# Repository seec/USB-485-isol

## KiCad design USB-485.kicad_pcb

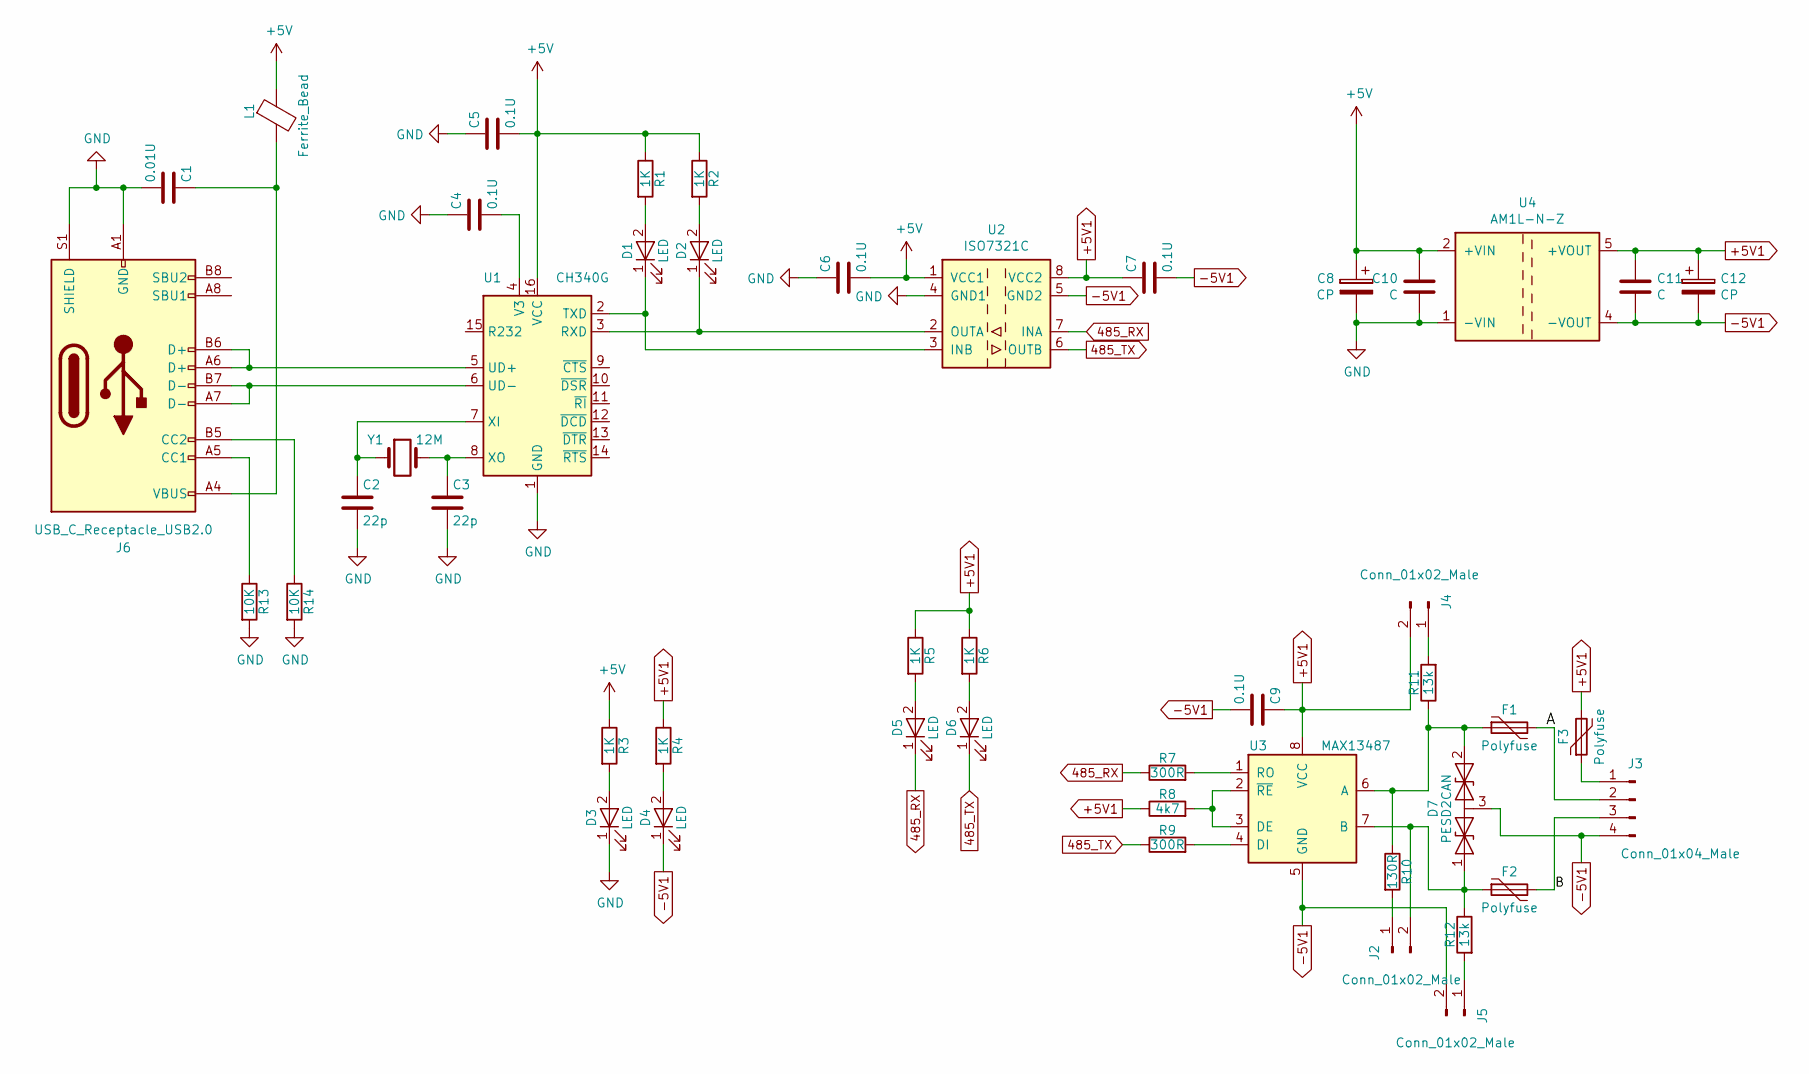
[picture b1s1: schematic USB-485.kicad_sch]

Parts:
C1: 0.01U; C_0805_2012Metric_Pad1.18x1.45mm_HandSolder
C2, C3: 22p; C_0805_2012Metric_Pad1.18x1.45mm_HandSolder
C4, C5, C6, C7, C9: 0.1U; C_0805_2012Metric_Pad1.18x1.45mm_HandSolder
C8, C12: CP; CP_Elec_5x5.3
C10, C11: C; C_0805_2012Metric_Pad1.18x1.45mm_HandSolder
D1, D2, D3, D4, D5, D6: LED; LED_D3.0mm
D7: PESD2CAN; SOT-23
F1, F2, F3: Polyfuse; Fuseholder_Littelfuse_Nano2_157x
J2, J4, J5: Conn_01x02_Male; PinHeader_1x02_P2.54mm_Vertical
J3: Conn_01x04_Male; TerminalBlock_MetzConnect_Type011_RT05504HBWC_1x04_P5.00mm_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
J6: USB_C_Receptacle_USB2.0; USB_C_Receptacle_HRO_TYPE-C-31-M-12
L1: Ferrite_Bead; L_Bourns-SRN4018
R1, R2, R3, R4, R5, R6: 1K; R_0805_2012Metric_Pad1.20x1.40mm_HandSolder
R7, R9: 300R; R_0805_2012Metric_Pad1.20x1.40mm_HandSolder
R8: 4k7; R_0805_2012Metric_Pad1.20x1.40mm_HandSolder
R10: 130R; R_0805_2012Metric_Pad1.20x1.40mm_HandSolder
R11, R12: 13k; R_0805_2012Metric_Pad1.20x1.40mm_HandSolder
R13, R14: 10K; R_0805_2012Metric_Pad1.20x1.40mm_HandSolder
U1: CH340G; SOIC-16_3.9x9.9mm_P1.27mm
U2: ISO7321C; SOIC-8_3.9x4.9mm_P1.27mm
U3: MAX13487; SOIC-8_3.9x4.9mm_P1.27mm
U4: AM1L-N-Z
Y1: 12M; Crystal_SMD_5032-2Pin_5.0x3.2mm

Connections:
485_RX: D5.1 (K), R7.1, U2.7 (INA)
485_TX: D6.1 (K), R9.1, U2.6 (OUTB)
+5V: C5.2, C6.2, C8.1, C10.1, L1.1, R1.1, R2.1, R3.1, U1.16 (VCC), U2.1 (VCC1), U4.2 (+VIN)
+5V1: C7.1, C9.1, C11.1, C12.1, F3.2, J4.2, R4.1, R5.1, R6.1, R8.1, U2.8 (VCC2), U3.8 (VCC), U4.5 (+VOUT)
-5V1: C7.2, C9.2, C11.2, C12.2, D4.1 (K), D7.3 (common), J3.4, J5.2, U2.5 (GND2), U3.5 (GND), U4.4 (-VOUT)
/A: F1.2, J3.2
/B: F2.2, J3.3
GND: C1.2, C2.2, C3.2, C4.1, C5.1, C6.1, C8.2, C10.2, D3.1 (K), J6.A1 (GND), J6.A12 (GND), J6.B1 (GND), J6.B12 (GND), J6.S1 (SHIELD), R13.2, R14.2, U1.1 (GND), U2.4 (GND1), U4.1 (-VIN)
unnamed: C1.1, J6.A4 (VBUS), J6.A9 (VBUS), J6.B4 (VBUS), J6.B9 (VBUS), L1.2
unnamed: D1.2 (A), R1.2
unnamed: D1.1 (K), U1.2 (TXD), U2.3 (INB)
unnamed: D2.2 (A), R2.2
unnamed: D2.1 (K), U1.3 (RXD), U2.2 (OUTA)
unnamed: D3.2 (A), R3.2
unnamed: D4.2 (A), R4.2
unnamed: D5.2 (A), R5.2
unnamed: D6.2 (A), R6.2
unnamed: D7.1 (A1), F2.1, J2.2, R12.1, U3.7 (B)
unnamed: D7.2 (A2), F1.1, R10.1, R11.1, U3.6 (A)
unnamed: J2.1, R10.2
unnamed: F3.1, J3.1
unnamed: J4.1, R11.2
unnamed: J5.1, R12.2
unnamed: J6.A5 (CC1), R13.1
unnamed: J6.B5 (CC2), R14.1
unnamed: J6.A6 (D+), J6.B6 (D+), U1.5 (UD+)
unnamed: J6.A7 (D-), J6.B7 (D-), U1.6 (UD-)
unnamed: C4.2, U1.4 (V3)
unnamed: C2.1, U1.7 (XI), Y1.1
unnamed: C3.1, U1.8 (XO), Y1.2
unnamed: R8.2, U3.2 (~RE), U3.3 (DE)
unnamed: R9.2, U3.4 (DI)
unnamed: R7.2, U3.1 (RO)

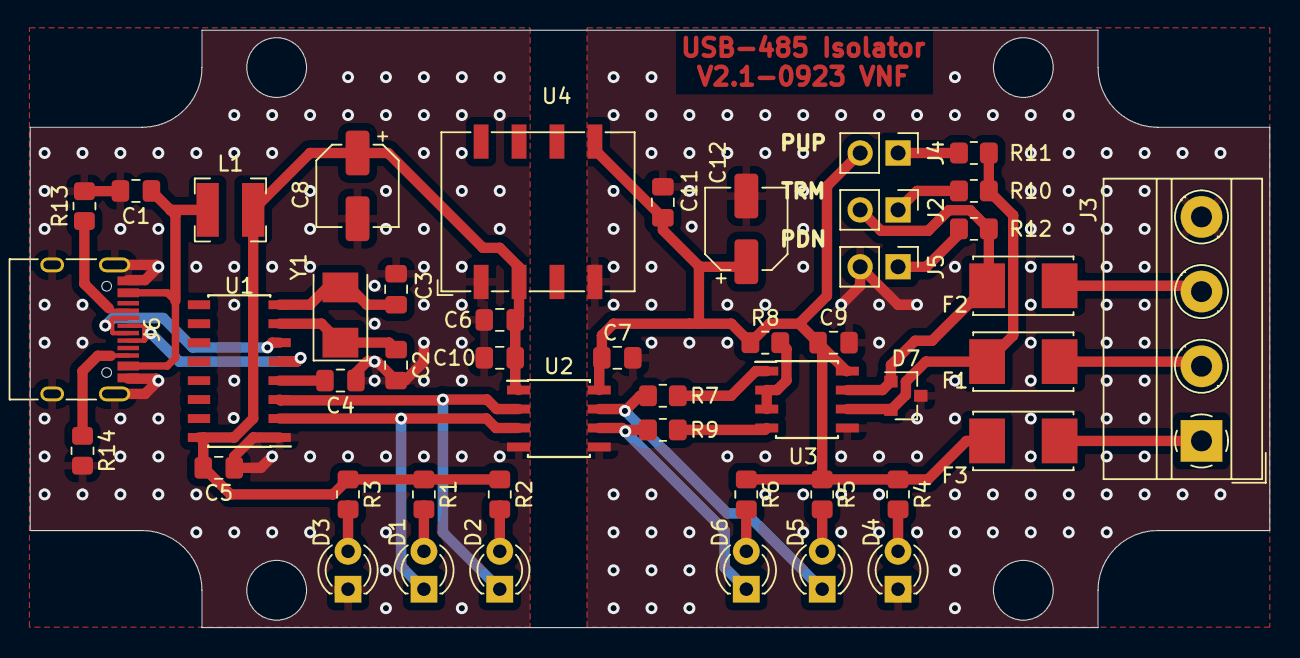
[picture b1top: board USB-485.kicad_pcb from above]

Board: 2 copper layers, 83.0 x 40.0 mm, 47 parts (0 on the bottom side), 33 nets.
